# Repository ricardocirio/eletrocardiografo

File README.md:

# Eletrocardiógrafo

Projeto para a disciplina PIN22107 do curso de Graduação em Engenharia Eletrônica do Instituto Federal de Santa Catarina. Consiste na concepção e execução de um eletrocardiógrafo de baixo consumo energético capaz de adquirir um sinal de eletrocardiograma por meio de 3 eletrodos e enviar suas medições para um aplicativo de aparelho celular.

## Especificações de projeto
* Energizado por bateria, portanto apresentando baixo consumo energético.

* Capaz de medir sinais entre 0,05 e 100 Hz, permitindo visualização e análise da morfologia do sinal cardíaco humano com propriedade.

## Etapas do projeto
* **Aquisição do sinal:** Por meio de eletrodos conectados ao paciente, verificando e garantindo a proteção do mesmo, com processo de isolamento do sistema. Os sinais obtidos diretamente dos eletrodos tem amplitude reduzida, atingindo 1 mV com uma frequência na faixa entre 0,05 e 100 Hz. Desse modo, para uma melhor visualização e manipulação, uma etapa de amplificação é necessária, tomando cuidado com a rejeição de ruído de modo comum.

* **Filtros:** Um filtro passa faixa deve ser implementado para seleção da banda de operação desejada, podendo ser composto por um passa altas em série com um passa baixas e, além disso, deve-se atentar para o fato de que a frequência da rede elétrica pode interferir no sinal e, portanto, deve ser removida por meio de um filtro rejeita faixa, com alto fator de qualidade.

* **Adequação do sinal:** Além de um ajuste de offset, é necessário implementar um controle de ganho que adeque a amplitude do sinal, preparando-o para digitalização por meio de um ADC.

* **Digitalização:**  A conversão do sinal analógico para digital pode ser realizada através de um conversor dedicado ou até mesmo por meio do conversor integrado de algum microcontrolador, como por exemplo o ATMEGA328p.

* **Processamento digital:** Envio dos dados via Bluetooth para o aplicativo de celular.

## Fluxograma
Para uma melhor organização e visualização das etapas necessárias, foi construído o seguinte fluxograma:

## Aquisição do sinal
Contando com um amplificador de instrumentação de alta relação sinal-ruído (SNR), o estágio inicial de amplificação faz a leitura do sinal diferencial entre os eletrodos esquerdo e direito, ao mesmo tempo que injeta uma referência por meio de um terceiro eletrodo conectado ao paciente.

O esquemático do circuito utilizado nesse estágio pode ser verificado a seguir, sendo baseado no circuito proposto e verificado na folha de dados do próprio fabricante:

## Filtros
Os filtros passa-baixas, passa-altas e rejeita-faixa foram projetados conforme o equacionamento descrito pelo livro "Amplificadores Operacionais e Filtros Ativos". As simulações foram realizadas no _software_ LTspice XVII. Foi definido inicialmente ganho unitário para todos os filtros.

### Passa-altas
Projetou-se o filtro passa-altas com ganho unitário na estrutura _voltage-controlled voltage source_ (VCVS).

Por meio do uso do software de simulação, o comportamento resultante do filtro é:

### Passa-baixas
Abaixo é possível seguir a sequência de passos utilizados na construção do filtro passa-baixas:

No intuito de otimizar a eficiência energética do eletrocardiógrafo, foi analisada a possibilidade de implementar um filtro passa-baixas passivo, portanto foi realizada uma comparação entre o filtro projetado de 2ª ordem com um filtro passivo na simulação.

Apesar da economia de componentes apresentada pelo filtro passivo, sua atenuação na banda passante é indesejada e, portanto, optou-se pela utilização do filtro de 2ª ordem, que apresenta ainda decaimento de 40 dB por década na rejeição e consequentemente um fator de qualidade mais elevado.

### Rejeita-faixa

Inicialmente, projetou-se o filtro notch ativo para rejeitar ruídos oriundos da rede elétrica de 60 Hz.

Entretanto, devido à sensibilidade deste filtro aos valores dos componentes utilizados, e a necessidade de um elevado fator de qualidade, concluiu-se que implementá-lo digitalmente seria uma alternativa mais apropriada. Além disso, pelo fato do circuito ser alimentado via bateria, a interferência da rede é fortemente reduzida, embora não completamente eliminada.

## Automatic Gain Control (AGC)

Ao longo do projeto, verificou-se que seria interessante a implementação de um ajuste de ganho automático devido à incerteza na amplitude do sinal de entrada, já que o mesmo varia conforme o biotipo do paciente e disposição dos eletrodos, possibilitando que a amplificação seja insuficiente ou demasiada.

Após analisar e estudar diversas maneiras de implementar um sistema de adequação do sinal, buscando obter uma excursão adequada e constante para diferentes amplitudes de entrada, surgiu como uma solução conveniente a ideia de um controle de ganho automático (AGC) por meio de um amplificador operacional não-inversor com a resistência de um JFET participando de sua realimentação negativa e influenciando diretamente em seu ganho de amplificação.

Embora seja possível controlar a resistência do JFET apropriadamente através da aplicação de um PWM gerado pelo microcontrolador que adquire o sinal, isso exige mais processamento do mesmo e consequentemente eleva seu consumo energético. Sendo assim, a alternativa escolhida foi a de controlar esse sistema de maneira analógica.

Com o auxílio do LTSpice, traçou-se, em simulação, a curva da resistência Rds em função da tensão Vgs do BF245B, transistor selecionado para o circuito.

É notável a grande variação em sua resistência que ocorre em um pequeno intervalo de variação de Vgs. Devido a isso, percebe-se que é por volta desse intervalo que o JFET deve operar. Logo, projetou-se um circuito para fechar a malha de realimentação do AGC, constituído de um retificador de precisão inversor com ajuste de ganho, que detecta e inverte a tensão de pico positiva do sinal, mantendo o valor negativo obtido, utilizado para controlar o estrangulamento no canal do transistor, controlando sua condutividade. 

O ajuste de ganho da realimentação, proporcionado pelo trimpot RV1, permite que se encontre o ponto ideal de operação do BF245B e também possibilita a definição de um valor limite para o sinal amplificado pelo AGC.

## Somador

Na intenção de adequar o sinal de saída para uma conversão AD fez com que surgisse a necessidade de inserir um deslocamento de nível no sinal de saída, o deixando completamente positivo. A maneira mais eficiente encontrada faz o uso de um circuito somador não-inversor, visto na figura a seguir:

Mesmo que várias fontes tratem o circuito inversor como mais indicado e até mesmo mais difundido, a escolha pela utilização de um somador não-inversor procurou manter a ideia de um estágio genérico entre os outros, sem levar em conta se o sinal que entrava nele era invertido ou não, já que a presença de um sinal invertido na saída pode ser corrigida com a simples inversão dos conectores dos eletrodos.

Outra parte importante no projeto do somador se deu pela adição de dois resistores de alto valor (1 Megaohm), de maneira a proporcionar um casamento entre as impedâncias de saída do AGC (a própria impedância de saída do amplificador utilizado) e a de entrada do somador (entrada do amplificador empregado).

## Hardware

* **Protótipo inicial**

Em um primeiro momento, para validar os circuitos projetados até aquele momento, optou-se pela confecção de um protótipo contendo apenas os estágios de aquisição e filtragem do sinal. Já na intenção de condicioná-lo para uma conversão AD, por meio de um microcontrolador, existiu a necessidade de um ajuste de _offset_, tornando o sinal de saída completamente positivo. 

A alternativa aparentemente mais prática e econômica foi a de inserir esse acréscimo no valor de tensão já no próprio filtro passa-altas, considerando que a topologia de um filtro ativo MFB (_Multiple Feedback_) permite um deslocamento do nível de tensão apenas injetando a tensão desejada na entrada não-inversora do amplificador operacional envolvido no circuito. Ao contrário do esperado, o _offset_ não se comportou corretamente, pois mesmo com ganho unitário nos filtros seguintes, o sinal de saída apresentou grande instabilidade.

Além disso, o ajuste de ganho do sistema foi inserido por meio de um potenciômetro em série com o resistor de ganho do AD620. Observou-se, entretanto, que essa topologia deixa a desejar pelos valores de ganho muito elevados para esse estágio, já que nele o sinal ainda não foi filtrado e portanto componentes em frequências indesejadas também são amplificadas.

Para ilustrar, a seguir, é possível ver o esquemático que descreve o circuito utilizado no protótipo inicial:

Percebe-se que o circuito é energizado por uma alimentação simétrica de 9V, proveniente de duas baterias. Ainda, abaixo é possível ver o layout da placa de circuito impresso resultante:

* **Placa final**

Levando em conta os problemas encontrados no protótipo inicial, a solução adotada com relação ao _offset_ foi de aplicá-lo em um estágio próprio, consistindo de um somador não-inversor, só no final do circuito, evitando que esse deslocamento de nível de tensão atrapalhasse o funcionamento das etapas anteriores, como os filtros e o próprio AGC.

Pensando no consumo energético e estabilidade do sistema, foi estabelecido que todos os circuitos seriam energizados com alimentação simétrica regulada de 3.3V. Por conseguinte, foi introduzida uma regulação da tensão de alimentação positiva utilizando o regulador linear _low-dropout_ LM1117. Em sequência, visando praticidade, projetou-se a obtenção da tensão de alimentação negativa através do inversor TPS60401. Isso flexibilizou o sistema com relação a sua tensão de entrada, podendo ser energizado por uma única bateria de valor de tensão entre 4.75 e 10V.

Outro ponto importante na construção e adequação do funcionamento da nova placa desenvolvida, consistiu na seleção dos ganhos envolvidos em cada etapa de maneira a manter um valor final de amplificação equilibrado que não trouxesse instabilidade ao conjunto. Um exemplo disso foi o ganho definido para o estágio do amplificador de instrumentação.

Por apresentar uma característica de amplificação com alta relação sinal-ruído (SNR), pareceu interessante o estabelecimento do maior ganho possível nesse estágio, de maneira a eliminar ao máximo o ruído do sinal adquirido. A seleção do ganho do circuito de aquisição é diretamente dependente do valor de resistência selecionado para o resistor R9, entre os pinos 1 e 8 do AD620 (estágio de aquisição). Na intenção de deixar o sistema independente de um ajuste manual, antes regulado pelo potenciômetro adicionado, a ideia passou a ser de fixar o valor desse resistor, inicialmente 75 ohms, resultando em um ganho próximo a 660. 

Com esse ganho estabelecido, a aquisição do sinal se deu de maneira eficiente, apresentando uma boa amplitude para o sinal de saída e uma satisfatória atenuação do ruído envolvido. Com a adição dos filtros, o sinal de saída alcançou as características desejadas para o circuito.

A partir da decisão de adicionar o estágio de controle de ganho, este proporcionou certas limitações em relação ao sinal condicionado pelos primeiros estágios: com um funcionamento adequado do AGC apenas para sinais de entrada com valores de tensão entre 50 e 500 mVpp, o ganho definido para o estágio de aquisição se tornou absurdo, já que o sinal fornecido ao estágio de controle automático de ganho já se encontrava fora dos limites determinados, deixando o sinal de saída instável e oscilando entre as saturações negativa e positiva do amplificador operacional, demonstrando um valor exagerado de amplificação.

Desse modo, ajustes foram feitos e um novo resistor tomou o lugar do R9, com valor igual a 1 kohms, resultando em um ganho próximo a 50 e permitindo que o ganho excedente necessário fosse proporcionado pelo próprio AGC. Com estes ajustes, os problemas de saturação foram corrigidos e o pleno funcionamento do estágio do AGC foi alcançado.
Funcionando como esperado, o somador não-inversor adicionado ao final cumpriu plenamente seu papel, resultando em uma saída do eletrocardiógrafo limitada a um valor de aproximadamente 1 Vpp e um _offset_ também de 1 VCC, adequado à janela estabelecida de 3.3 V limitados pela alimentação do sistema, que também acaba ditando o valor máximo de tensão para o ADC.

Por fim, o resultado foi uma placa de circuito impresso, empregando dessa vez alguns componentes do tipo SMD disponíveis para o projeto, de maneira a distribuí-los melhor e diminuir o tamanho físico de placa necessário para a construção do projeto.

## Software

Depois de todo o processo de construção do eletrocardiógrafo, dispositivo preocupado em evidenciar o formato do sinal emitido pela pulsação cardiovascular, é importante encontrar uma maneira de mostrar graficamente a saída do conjunto. Para esta tarefa, a escolha de uma conexão por meio de um transmissor Bluetooth visou a praticidade de uma conexão sem fio e também por ser uma ferramenta democrática, já que todos os smartphones atuais contam com esse tipo de conexão, o que leva à criação de um produto de mais fácil utilização e adaptação.

O transmissor Bluetooth escolhido para a tarefa é um módulo do tipo HC-05, que utiliza a comunicação UART do microcontrolador para receber e enviar informações do mesmo. Para a visualização gráfica, foi utilizado um aplicativo para smartphones com sistema operacional Android, gratuito, e facilmente encontrado na loja de aplicativos. Nesse aplicativo, o envio de uma _string_ contendo o valor lido no ADC em um formato reconhecido pelo software permitiu que a onda fosse visualizada de maneira bem prática.  

## Resultados

Depois de toda a etapa de projeto, é importante a validação dos resultados esperados, verificando se os objetivos do projeto foram alcançados. 

Na figura a seguir, é possível verificar o sinal de saída do eletrocardiógrafo, obtido com o auxílio de um osciloscópio:

O sinal visto na imagem acima traz algumas informações importantes sobre as validações do projeto: primeiramente, é possível ver um sinal de mais alta frequência sobreposto ao do ECG, este que é a influência eletromagnética causada pela própria rede de distribuição, com sua frequência de 60 Hz, e que acaba afetando o circuito que é eletromagneticamente sensível. Além disso, frequências muito mais altas podem ser verificadas sobre o sinal, na ordem dos MHz, provenientes de ondas de radiofrequência que transitam pelo ambiente e que não conseguem ser filtradas.

A presença da frequência de 60 Hz na saída do circuito era esperada, já que esta se encontra na faixa de operação do sistema (0.05 - 100 Hz), e deveria ser eliminada pelo filtro rejeita-faixa idealizado anteriormente mas que, por sua alta precisão de projeto, se tornou inviável. Parte dessa interferência já é diminuída por conta do uso de baterias para a alimentação do circuito, isolando o circuito de ruídos conduzidos, entretanto, não o blindando de possíveis ruídos irradiados. Na parte da medição, o uso de um osciloscópio desligado da rede, também alimentado por baterias, permitiu a visualização do sinal também com menor interferência.

No caso das componentes de mais alta frequência, idealmente, essas deveriam ser eliminadas pelo filtro passa-baixas implementado, evitando essa interferência. O que acontece, é que na prática o amplificador operacional utilizado nos filtros não é capaz de trabalhar em frequências muito altas, como as presentes no sinal. O modelo que usamos para a implementação (LM324) tem um bom funcionamento para frequências até a ordem de algumas centenas de kHz, no máximo poucos MHz, o que o deixa impossibilitado de eliminar as frequências indesejadas. Por questão de esclarecimento, foi testado isoladamente o filtro passa-baixas e verificado que sua frequência de corte se encontra nos 100 Hz esperados e que os ruídos decorrem mesmo da não-idealidade do amplificador operacional. 

Com a praticidade do osciloscópio, independente da rede de energia, foi possível desligar os outros equipamentos ligados nos arredores da montagem, verificando o nível de interferência de sua emissão de ondas eletromagnéticas. Ainda, o uso de um limitador de banda do osciloscópio, com o intuito de facilitar a visualização, eliminando as frequências que o próprio circuito era incapaz de lidar, resultou na imagem a seguir:

Em relação ao sinal visualizado por meio do aplicativo, empregando uma conexão Bluetooth, pode ser vista a seguir uma captura da tela do smartphone utilizado:

O sinal verificado no aplicativo não apresenta as componentes de frequência da ordem dos MHz, isso por conta da própria taxa de amostragem do sinal e da transmissão do Bluetooth, que acabam por “alisar” a curva.

## Consumo energético

O consumo da placa final de aquisição e condicionamento do sinal é estimado em aproximadamente 135.9mW. Esse valor representa o “pior caso”, pois foi obtido considerando: o consumo máximo de 1,2mA em cada canal dos LM324, incluindo os dois não utilizados; a corrente máxima de 1,3mA do AD620; a potência dissipada no regulador LM1119, considerando a bateria de 9V utilizada nos testes; e a eficiência de cerca de 97,5% do inversor TPS60401, apresentada quando o mesmo opera em 3,3V suprimindo as correntes de alimentação mencionadas para os amplificadores operacionais e de instrumentação.

Analisando à parte a potência dissipada pela parte digital do sistema, verifica-se que o microcontrolador ATmega328p consome cerca de 16,5mW operando ativamente em 16MHz e alimentado com +3,3V. Já o módulo bluetooth apresenta consumo médio de 82,5mW.

Considerando uma bateria de 9V comum, fornecendo uma quantidade de energia próxima a 500mAh, seria possível alimentar o circuito responsável pela aquisição e condicionamento do sinal (sem a transmissão bluetooth) por até 33 horas ininterruptas, com esse tempo podendo aumentar significativamente ao usar baterias com maior capacidade. Se o microcontrolador e módulo bluetooth forem considerados, o funcionamento ininterrupto sob as condições mencionadas chega a 19 horas.

## Sugestões para trabalhos futuros

* Naturalmente, algumas melhorias podem ser feitas a fim de se conseguir melhores resultados com o circuito implementado: para diminuir a interferência do sinal oscilatório de 60 Hz, proveniente da rede, seria possível a implementação de um filtro rejeita-faixa digital, utilizando o próprio microcontrolador que nesse momento faz apenas o trabalho da transmissão Bluetooth;

* Como maneira de blindar o circuito contra as interferências eletromagnéticas, a construção do circuito envolvido por um gabinete metálico traria melhores resultados, minimizando tanto a interferência da rede elétrica quanto as altas frequências que conseguem passar pelos filtros.

* O consumo energético pode ser minimizado ainda mais com a utilização de baterias de tensão próxima à mínima suportada, redução da frequência de operação do microcontrolador, bem como desabilitação de seus periféricos não utilizados e possivelmente utilização do modo _sleep_ entre leituras do ADC e envio de dados via bluetooth.

## Autores
* João Vitor Bassani
* Ricardo Cirio

## Bibliografia
1. PERTENCE Jr., A. **Amplificadores Operacionais e Filtros Ativos**. 7.ed. Porto Alegre: Artmed, 2012.

2. SEDRA, A. S; SMITH, K. C. **Microeletrônica**. 5 ed. São Paulo: Pearson / Prentice Hall, 2010.

3. BOYLESTAD, R. e NASHELSKY, L. **Dispositivos eletrônicos e teoria de circuitos**. 8 ed. Prentice Hall do Brasil. Rio de Janeiro. 2005.

4. Analog Devices. **AD620**. Disponível em: <https://www.analog.com/media/en/technical-documentation/data-sheets/AD620.pdf>. Acesso em 16/12/2018.

5. On Semiconductor. **LM324**. Disponível em: <https://www.onsemi.com/pub/Collateral/LM324-D.PDF>. Acesso em 16/12/2018.

6. Texas Instruments. **LM1117**. Disponível em: <http://www.ti.com/lit/ds/symlink/lm1117.pdf>. Acesso em 16/12/2018.

7. Texas Instruments. **TPS6040x**. Disponível em: <http://www.ti.com/lit/ds/symlink/tps60400.pdf>. Acesso em 16/12/2018.

8. Atmel. **ATmega328P**. Disponível em: <http://ww1.microchip.com/downloads/en/DeviceDoc/Atmel-7810-Automotive-Microcontrollers-ATmega328P_Datasheet.pdf>. Acesso em 16/12/2018.

9. Makezine. **HC Serial Bluetooth Products**. Disponível em: <https://cdn.makezine.com/uploads/2014/03/hc_hc-05-user-instructions-bluetooth.pdf>. Acesso em 16/12/2018.

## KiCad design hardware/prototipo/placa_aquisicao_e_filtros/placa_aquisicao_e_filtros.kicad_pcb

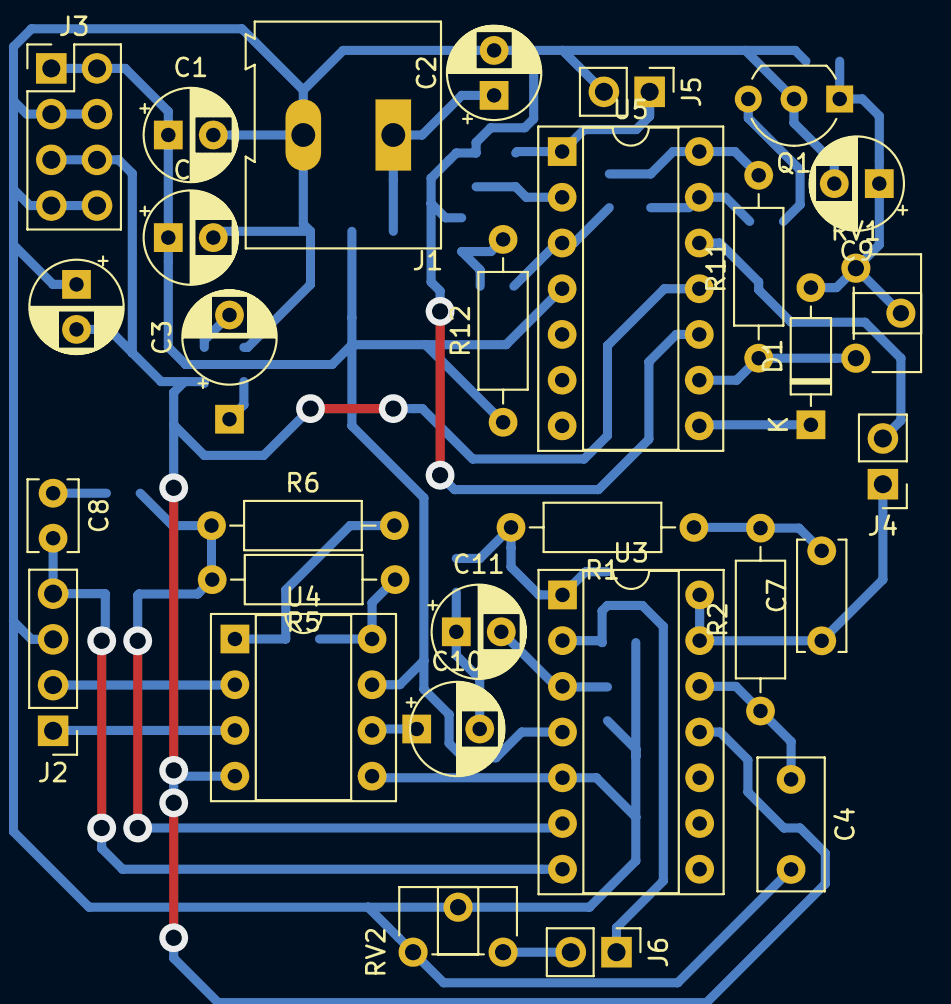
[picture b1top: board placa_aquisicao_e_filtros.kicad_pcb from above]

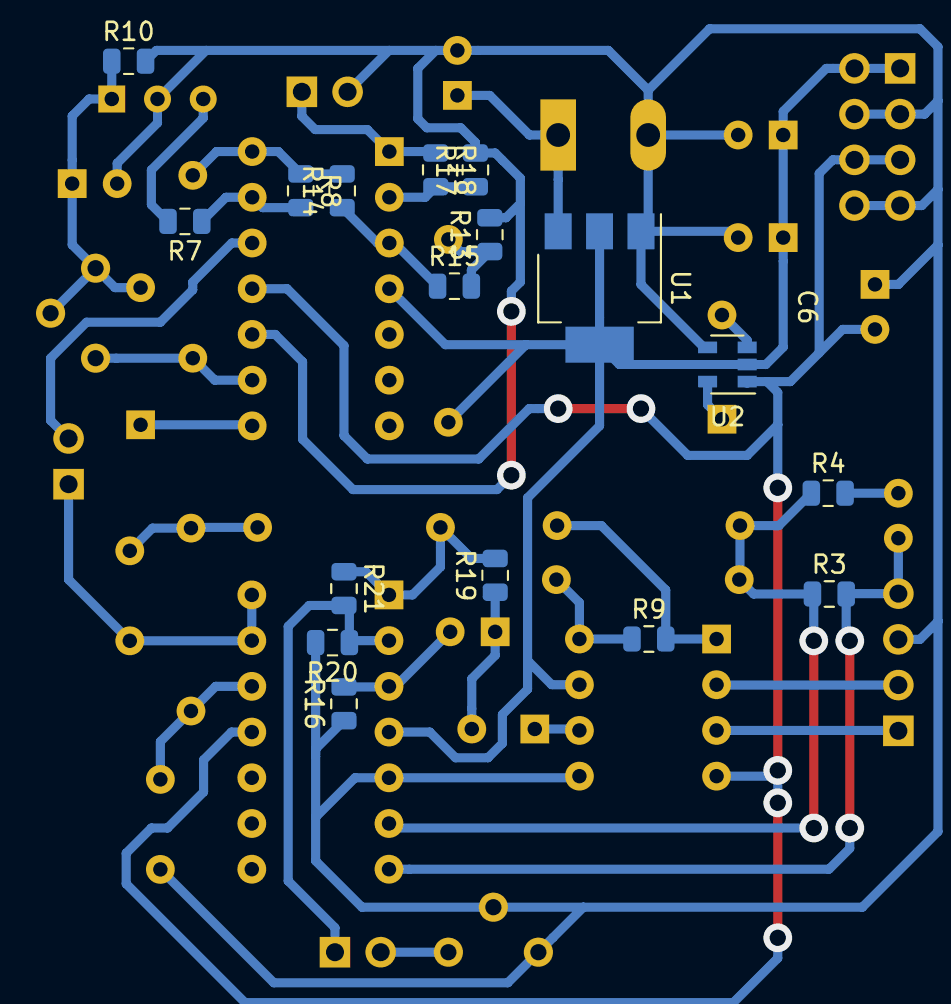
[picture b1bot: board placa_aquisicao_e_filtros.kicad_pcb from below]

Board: 2 copper layers, 47 parts (17 on the bottom side), 33 nets.

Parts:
C1, C3, C6: 1u; CP_Radial_D5.0mm_P2.50mm
C2, C5: 10u; CP_Radial_D5.0mm_P2.50mm
C4: 47n; C_Rect_L7.2mm_W3.5mm_P5.00mm_FKS2_FKP2_MKS2_MKP2
C7: 100n; C_Disc_D6.0mm_W2.5mm_P5.00mm
C8: 100p; C_Disc_D3.8mm_W2.6mm_P2.50mm
C9: 22u; CP_Radial_D5.0mm_P2.50mm
C10, C11: 47u; CP_Radial_D5.0mm_P2.50mm
D1: 1N4148; D_DO-35_SOD27_P7.62mm_Horizontal
J1: Conn_01x02; TerminalBlock_Altech_AK300-2_P5.00mm
J2: Conn_01x04; PinHeader_1x04_P2.54mm_Vertical
J3: Conn_02x04_Counter_Clockwise; PinHeader_2x04_P2.54mm_Vertical
J4, J5, J6: Conn_01x02; PinHeader_1x02_P2.54mm_Vertical
Q1: BF245B; TO-92_Inline_Wide
R1: 18k; R_Axial_DIN0207_L6.3mm_D2.5mm_P10.16mm_Horizontal
R2: 30k; R_Axial_DIN0207_L6.3mm_D2.5mm_P10.16mm_Horizontal
R3: 1M; R_0805_2012Metric
R4, R8, R17, R18: 12k; R_0805_2012Metric
R5, R6: 24k; R_Axial_DIN0207_L6.3mm_D2.5mm_P10.16mm_Horizontal
R7: 560R; R_0805_2012Metric
R9: 75R; R_0805_2012Metric
R10, R19: 100k; R_0805_2012Metric
R11: 200k; R_Axial_DIN0207_L6.3mm_D2.5mm_P10.16mm_Horizontal
R12: 51k; R_Axial_DIN0207_L6.3mm_D2.5mm_P10.16mm_Horizontal
R13: 22k; R_0805_2012Metric
R14, R15: 1k; R_0805_2012Metric
R16: 47k; R_0805_2012Metric
R20: 68k; R_0805_2012Metric
R21: 150k; R_0805_2012Metric
RV1: 470k; Potentiometer_ACP_CA6-H2,5_Horizontal
RV2: R_POT; Potentiometer_ACP_CA6-H2,5_Horizontal
U1: AP1117-33; SOT-223-3_TabPin2
U2: TPS60401; SOT-23-5
U3, U5: Opamp_Quad_Generic; DIP-14_W7.62mm_Socket
U4: AD620; DIP-8_W7.62mm_Socket

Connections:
+3V3: C1.1, C5.1, J3.1, J3.2, R12.1, U1.2, U2.2, U3.4, U4.7, U5.4
+Vin: C2.1, J1.1, U1.3
-3V3: C6.2, J3.5, J3.6, U2.1, U3.11, U4.4, U5.11
AGC: C7.1, J4.1, U3.13, U3.14
GNDA: C1.2, C2.2, C4.2, C5.2, C6.1, C9.2, J1.2, J2.3, J3.3, J3.4, J3.7, J3.8, J5.2, Q1.2, R10.2, R13.2, R16.1, R17.2, R20.2, RV2.1, RV2.2, U1.1, U2.4, U3.5, U4.5, U5.10
HP: C10.1, U4.6
LP: R1.2, R19.2, R21.1, U3.1
unnamed: C3.1, U2.5
unnamed: C3.2, U2.3
unnamed: C4.1, R2.1, U3.12
unnamed: C7.2, R1.1, R2.2
unnamed: C8.1, R4.2
unnamed: C9.1, D1.2, Q1.1, R10.1, RV1.1, RV1.2
unnamed: C10.2, C11.1, R19.1
unnamed: C11.2, R16.2, U3.3
unnamed: D1.1, U5.8
unnamed: J4.2, U5.12
unnamed: J6.1, R20.1, R21.2, U3.2
unnamed: J6.2, RV2.3
unnamed: Q1.3, R7.2
unnamed: R3.1, R4.1, R5.2, R6.1, U3.6
unnamed: R5.1, R9.1, U4.8
unnamed: R6.2, R9.2, U4.1
unnamed: R7.1, R8.2, U5.13
unnamed: R11.1, RV1.3, U5.9
unnamed: R12.2, R13.1, R15.2
unnamed: R14.1, R15.1, U5.3
unnamed: R17.1, R18.2, U5.2
OUT: J5.1, R18.1, U5.1
SUM: R8.1, R11.2, R14.2, U5.14
left_electrode: J2.1, U4.3
ref_electrode: C8.2, J2.4, R3.2, U3.7
right_electrode: J2.2, U4.2

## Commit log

2018-09-06 Initial commit.
2018-09-06 Changes in README.md
2018-09-06 Correção no fluxograma.
2018-09-06 Remoção do cronograma.
2018-09-06 Cronograma disponível na pasta de imagens.
2018-09-21 Filter simulations added.
2018-09-21 README fix.
2018-09-27 Acquisition PCB prototype started.
2018-09-28 Acquisition PCB prototype in development.
2018-10-05 Acquisition prototype board finalized.
2018-12-01 PCB with AGC routed but negative supply without voltage regulator
2018-12-12 Second prototype working with bluetooth.
2018-12-12 Image size test.
2018-12-12 Center image.
2018-12-12 Center images.
2018-12-12 Image fix.
2018-12-16 Documentation added.
